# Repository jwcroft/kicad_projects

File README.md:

# kicad_projects
Incremental backups in case kicad decides to break itself again...

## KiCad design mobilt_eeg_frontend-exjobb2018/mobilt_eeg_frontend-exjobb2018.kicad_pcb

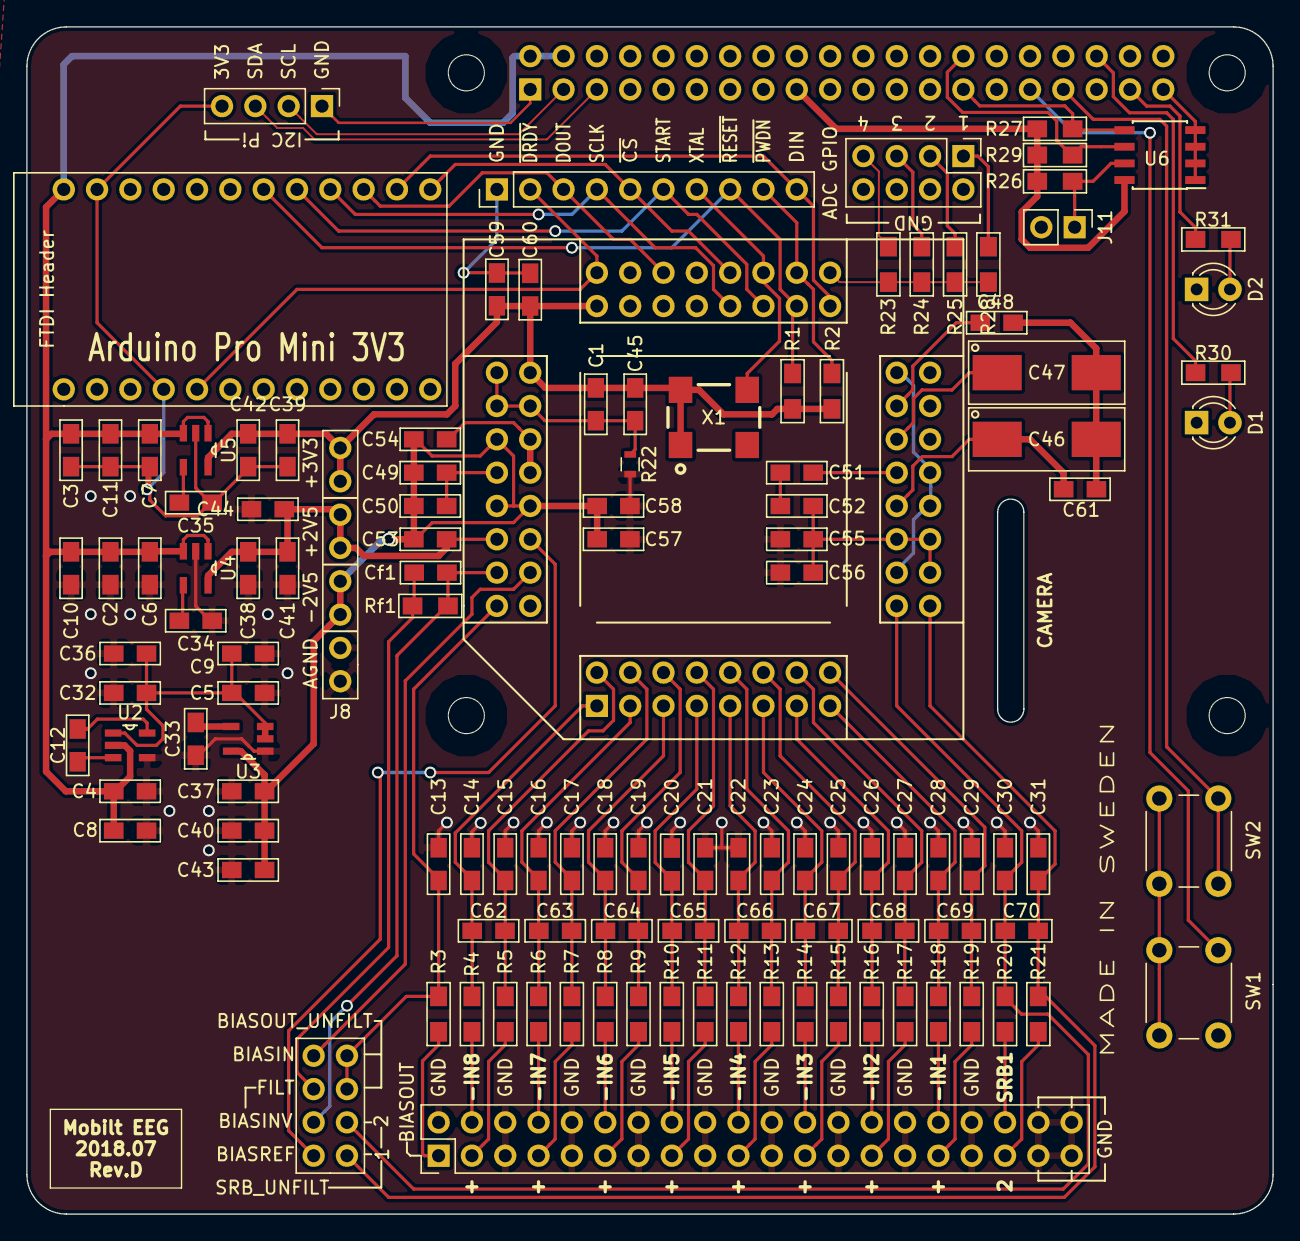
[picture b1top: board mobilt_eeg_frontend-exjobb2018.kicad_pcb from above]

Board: 2 copper layers, 95.0 x 90.5 mm, 127 parts (1 on the bottom side), 84 nets.

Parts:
C1, C10, C11, C43, C44, C50, C56, C58, C60, C61: 100nF; C_0805_HandSoldering_enclosed_footprint
C2, C3, C4, C5, C32, C37, C38, C39: 10uF; C_0805_HandSoldering_enclosed_footprint
C6, C7, C8, C12, C36, C45, C48, C49, C51, C52, C53, C54, C55, C57, C59: 1uF; C_0805_HandSoldering_enclosed_footprint
C9, C40, C41, C42: 2.2uF; C_0805_HandSoldering_enclosed_footprint
C13, C14, C15, C16, C17, C18, C19, C20, C21, C22, C23, C24, C25, C26, C27, C28, C29, C30, C31: 4.7nF; C_0805_HandSoldering_enclosed_footprint
C33, C34, C35: 10nF; C_0805_HandSoldering_enclosed_footprint
C46: 10uF; CP_Tantalum_Case-D_EIA-7343-31_Hand
C47: 100uF; CP_Tantalum_Case-D_EIA-7343-31_Hand
C62, C63, C64, C65, C66, C67, C68, C69, C70: DNP; C_0805_HandSoldering_enclosed_footprint
Cf1: 1.5nF; C_0805_HandSoldering_enclosed_footprint
D1, D2: LED; LED_D3.0mm
J1, J3: Conn_02x04_Odd_Even; Pin_Header_Straight_2x04_Pitch2.54mm
J2: Conn_02x20_Odd_Even; Pin_Header_Straight_2x20_Pitch2.54mm
J5: Data Header; Pin_Header_Straight_1x10_Pitch2.54mm
J8: Conn_01x08; Pin_Header_Straight_1x08_Pitch2.54mm
J9: Conn_01x04; Pin_Header_Straight_1x04_Pitch2.54mm
J11: Conn_01x02; Pin_Header_Straight_1x02_Pitch2.54mm
MK1, MK2, MK3, MK4: M2.5; MountingHole_2.7mm_M2.5
P1: Conn_02x20_Odd_Even; PinSocket_2x20_P2.54mm_Vertical
R1, R2, R23, R24, R25, R26, R28: 10k; R_0805_HandSoldering_enclose_footprint
R3, R4, R5, R6, R7, R8, R9, R10, R11, R12, R13, R14, R15, R16, R17, R18, R19, R20, R21: 4.99k 1%; R_0805_HandSoldering_enclose_footprint
R22: 0; R_0603
R27, R29: 3.9k; R_0805_HandSoldering_enclose_footprint
R30, R31: 1k; R_0805_HandSoldering_enclose_footprint
Rf1: 1M; R_0805_HandSoldering_enclose_footprint
SW1, SW2: SW_DIP_x01; SW_PUSH_6mm_h5mm
U1: ADS1299-4PAG; xQFP_64_to_2.54mm_adapter
U2: TPS60403DBVR; SOT95P280X145-5N
U3: TPS72325DBVT; SOT95P280X145-5N
U4: TPS73225DBVT; SOT95P280X145-5N
U5: TPS73233DBVT; SOT95P280X145-5N
U6: CAT24C256; SOIC-8_3.9x4.9mm_Pitch1.27mm
U7: arduino_pro_mini_3V3_sparkfun
X1: X1G0044810050_SG7050CAN_2.048_MHZ; SG0705

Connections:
+5V: C2.1, C3.1, C4.1, C6.1, C7.1, C8.1, C10.1, C11.1, P1.2, P1.4, U2.2, U4.1, U4.3, U5.1, U5.3, U7.24
/+3V3_Pi: J9.1, P1.1, P1.17, R26.2, R27.1, R29.1, U6.8
/-5V_unreg: C5.1, C9.1, C32.1, C36.1, U2.1, U3.2, U3.3
/BIASIN: J3.8, U1.62
/BIASINV: Cf1.1, J3.4, Rf1.1, U1.61
/BIASOUT: C13.1, J3.5, J3.7, R3.1, U1.63
/BIASOUT_FILTERED: J2.1, R3.2
/BIASREF: J3.2, U1.60
/GPIO1: J1.1, R28.2, U1.42
/GPIO2: J1.3, R25.2, U1.44
/GPIO2(SDA1): J9.2, P1.3
/GPIO3: J1.5, R24.2, U1.45
/GPIO3(SCL1): J9.3, P1.5
/GPIO4: J1.7, R23.2, U1.46
/GPIO6: P1.31, SW1.1
/GPIO13(PWM1): P1.33, SW2.1
/GPIO16: P1.36, R30.2
/GPIO26: P1.37, R31.2
/ID_SC: P1.28, R29.2, U6.6
/ID_SD: P1.27, R27.2, U6.5
/IN1N: C28.1, C69.1, R18.1, U1.15
/IN1P: C29.2, C69.2, R19.1, U1.16
/IN2N: C26.1, C68.1, R16.1, U1.13
/IN2P: C27.2, C68.2, R17.1, U1.14
/IN3N: C24.1, C67.1, R14.1, U1.11
/IN3P: C25.2, C67.2, R15.1, U1.12
/IN4N: C22.1, C66.1, R12.1, U1.9
/IN4P: C23.2, C66.2, R13.1, U1.10
/IN5N: C20.1, C65.1, R10.1, U1.7
/IN5P: C21.2, C65.2, R11.1, U1.8
/IN6N: C18.1, C64.1, R8.1, U1.5
/IN6P: C19.2, C64.2, R9.1, U1.6
/IN7N: C16.1, C63.1, R6.1, U1.3
/IN7P: C17.2, C63.2, R7.1, U1.4
/IN8N: C14.1, C62.1, R4.1, U1.1
/IN8P: C15.2, C62.2, R5.1, U1.2
/SPI_MISO: J5.3, U7.15
/SPI_MOSI: J5.10, U7.14
/SPI_SCK: J5.4, U1.40, U7.16
/SPI_SS: J5.5, U1.39, U7.13
/SRB1: C31.2, C70.2, J3.1, R21.1, U1.17
/SRB1_FILT: J2.36, R20.2
/SRB2: C30.1, C70.1, J3.3, R20.1, U1.18
/SRB2_FILT: J2.35, R21.2
/START: J5.6, P1.26, U1.38, U7.17
/VCAP1: C47.1, U1.28
/VCAP2: C48.2, U1.30
/VCAP3: C49.2, C50.2, U1.55
/VCAP4: C51.2, U1.26
/VREFP: C46.1, C61.1, U1.24
/XTAL: J5.7, U1.37, X1.3
/~DRDY: J5.2, U1.47, U7.5
/~PWDN: J5.9, P1.32, R2.2, U1.35, U7.19
/~RESET: J5.8, P1.29, R1.2, U1.36, U7.18
AGND: C2.2, C4.2, C5.2, C6.2, C8.2, C9.2, C10.2, C13.2, C14.2, C15.1, C16.2, C17.1, C18.2, C19.1, C20.2, C21.1, C22.2, C23.1, C24.2, C25.1, C26.2, C27.1, C28.2, C29.1, C30.2, C31.1, C32.2, C33.2, C34.2, C36.2, C37.2, C38.2, C40.2, C41.2, C43.2, C44.2, C55.1, C56.1, C57.1, C58.1, J2.2, J2.5, J2.6, J2.9, J2.10, J2.13, J2.14, J2.17, J2.18, J2.21, J2.22, J2.25, J2.26, J2.29, J2.30, J2.33, J2.34, J2.37, J2.38, J2.39, J2.40, J8.1, J8.2, R22.2, U2.4, U3.1, U4.2
AVDD: C38.1, C41.1, C44.1, C52.2, C53.2, C54.2, C55.2, C56.2, J8.5, J8.6, U1.19, U1.21, U1.22, U1.54, U1.56, U1.59, U4.5
AVSS: C37.1, C40.1, C43.1, C46.2, C47.2, C48.1, C49.1, C50.1, C51.1, C52.1, C53.1, C54.1, C57.2, C58.2, C61.2, J8.3, J8.4, U1.20, U1.23, U1.25, U1.32, U1.53, U1.57, U1.58, U3.5
DGND: C1.2, C3.2, C7.2, C11.2, C35.2, C39.2, C42.2, C45.2, C59.1, C60.1, D1.1, D2.1, J1.2, J1.4, J1.6, J1.8, J5.1, J9.4, J11.2, P1.6, P1.9, P1.14, P1.20, P1.25, P1.30, P1.34, P1.39, R22.1, R23.1, R24.1, R25.1, R28.1, SW1.2, SW2.2, U1.31, U1.33, U1.41, U1.49, U1.51, U1.52, U5.2, U6.1, U6.2, U6.3, U6.4, U7.4, U7.23, X1.2
DVDD: C1.1, C39.1, C42.1, C45.1, C59.2, C60.2, J8.7, J8.8, R1.1, R2.1, U1.48, U1.50, U5.5, X1.1, X1.4
unnamed: C12.1, U2.3
unnamed: C12.2, U2.5
unnamed: C33.1, U3.4
unnamed: C34.1, U4.4
unnamed: C35.1, U5.4
unnamed: Cf1.2, J3.6, Rf1.2
unnamed: D1.2, R30.1
unnamed: D2.2, R31.1
unnamed: J2.3, R5.2
unnamed: J2.4, R4.2
unnamed: J2.7, R7.2
unnamed: J2.8, R6.2
unnamed: J2.11, R9.2
unnamed: J2.12, R8.2
unnamed: J2.15, R11.2
unnamed: J2.16, R10.2
unnamed: J2.19, R13.2
unnamed: J2.20, R12.2
unnamed: J2.23, R15.2
unnamed: J2.24, R14.2
unnamed: J2.27, R17.2
unnamed: J2.28, R16.2
unnamed: J2.31, R19.2
unnamed: J2.32, R18.2
unnamed: J11.1, R26.1, U6.7

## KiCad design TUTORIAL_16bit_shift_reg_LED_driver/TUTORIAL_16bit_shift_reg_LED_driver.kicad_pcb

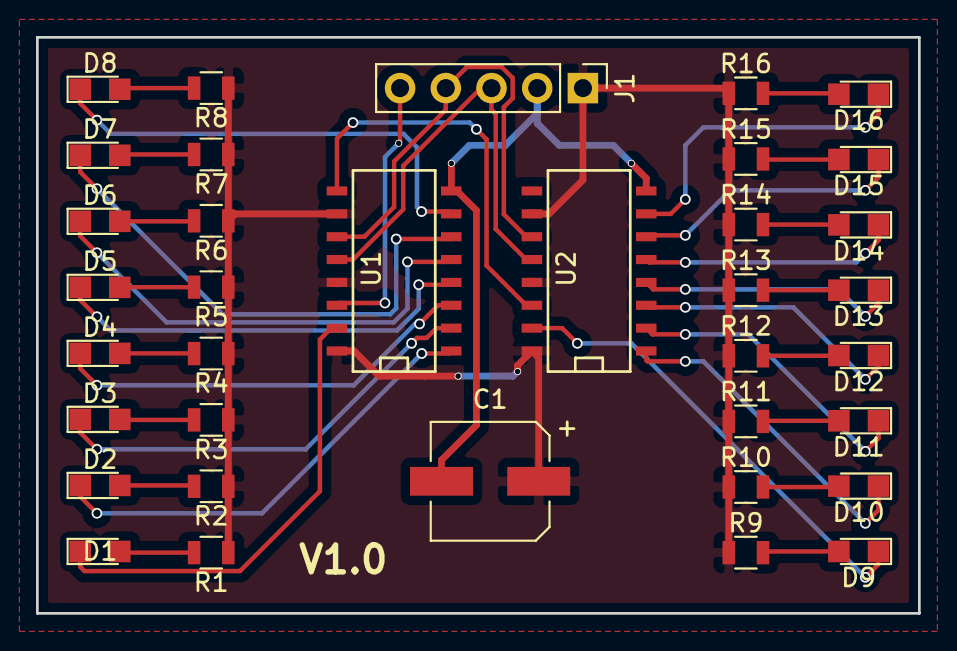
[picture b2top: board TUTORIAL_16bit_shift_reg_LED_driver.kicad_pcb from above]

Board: 2 copper layers, 49.0 x 32.0 mm, 36 parts (0 on the bottom side), 38 nets.

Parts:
C1: 200uF; CP_Elec_6.3x5.3
D1, D2, D3, D4, D5, D6, D7, D8, D9, D10, D11, D12, D13, D14, D15, D16: LED_ALT; LED_0805
J1: Conn_01x05_Male; Pin_Header_Straight_1x05_Pitch2.54mm
R1, R2, R3, R4, R5, R6, R7, R8, R9, R10, R11, R12, R13, R14, R15, R16: R; R_0805
U1, U2: 74HC595; SO-16-N

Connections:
/CLOCK: J1.4, U1.11, U2.11
/DATA: J1.5, U1.14
/DATA_S: U1.9, U2.14
/LATCH: J1.3, U1.12, U2.12
/led_1_1: D1.1, U1.15
/led_1_2: D2.1, U1.1
/led_1_3: D3.1, U1.2
/led_1_4: D4.1, U1.3
/led_1_5: D5.1, U1.4
/led_1_6: D6.1, U1.5
/led_1_7: D7.1, U1.6
/led_1_8: D8.1, U1.7
/led_2_1: D9.1, U2.15
/led_2_2: D10.1, U2.1
/led_2_3: D11.1, U2.2
/led_2_4: D12.1, U2.3
/led_2_5: D13.1, U2.4
/led_2_6: D14.1, U2.5
/led_2_7: D15.1, U2.6
/led_2_8: D16.1, U2.7
GND: C1.2, J1.2, U1.8, U2.8
unnamed: D1.2, R1.2
unnamed: D2.2, R2.2
unnamed: D3.2, R3.2
unnamed: D4.2, R4.2
unnamed: D5.2, R5.2
unnamed: D6.2, R6.2
unnamed: D7.2, R7.2
unnamed: D8.2, R8.2
unnamed: D9.2, R9.2
unnamed: D10.2, R10.2
unnamed: D11.2, R11.2
unnamed: D12.2, R12.2
unnamed: D13.2, R13.2
unnamed: D14.2, R14.2
unnamed: D15.2, R15.2
unnamed: D16.2, R16.2
VCC: C1.1, J1.1, R1.1, R2.1, R3.1, R4.1, R5.1, R6.1, R7.1, R8.1, R9.1, R10.1, R11.1, R12.1, R13.1, R14.1, R15.1, R16.1, U1.10, U1.13, U1.16, U2.10, U2.13, U2.16

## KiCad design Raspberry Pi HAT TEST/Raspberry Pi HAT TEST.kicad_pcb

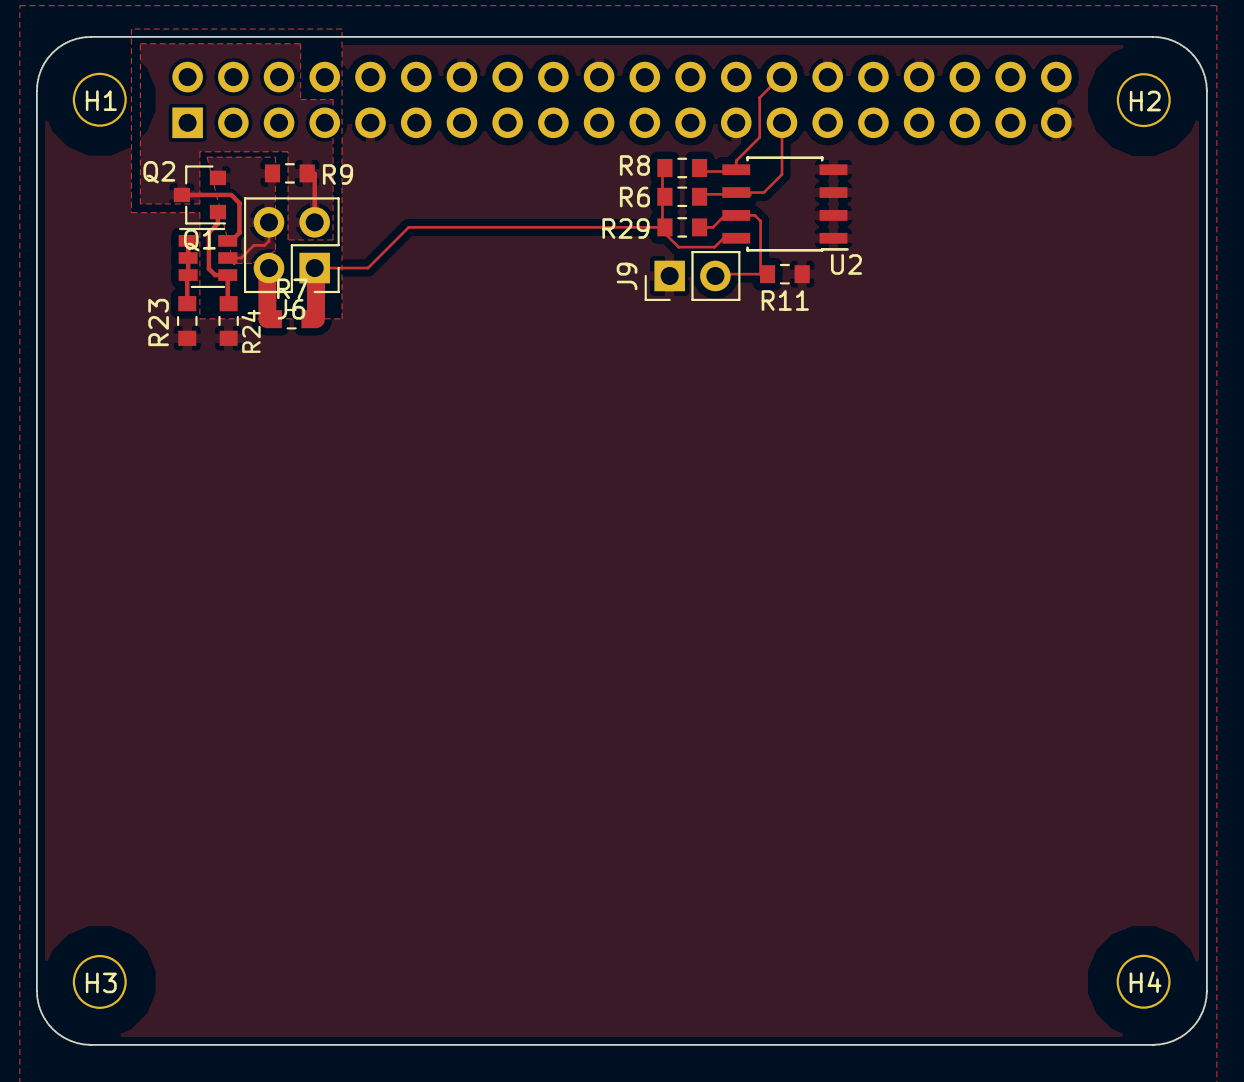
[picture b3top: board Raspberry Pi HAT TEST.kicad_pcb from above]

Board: 4 copper layers, 65.0 x 56.0 mm, 18 parts (1 on the bottom side), 10 nets.

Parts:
H1, H2, H3, H4: 3mm_Mounting_Hole; NPTH_3mm_ID
J3: 40HAT; PinSocket_2x20_P2.54mm_Vertical
J6: CONN_02X02; PinHeader_2x02_P2.54mm_Vertical
J9: CONN_01X02; PinHeader_1x02_P2.54mm_Vertical
Q1: DMG2305UX; SOT-23
Q2: DMMT5401; SOT-23-6
R6, R8: 3.9K; R_0603_1608Metric_Pad0.84x1.00mm_HandSolder
R7, R9, R11: DNP; R_0603_1608Metric_Pad0.84x1.00mm_HandSolder
R23, R24: 22; R_0603_1608Metric_Pad0.84x1.00mm_HandSolder
R29: 10K; R_0603_1608Metric_Pad0.84x1.00mm_HandSolder
U2: CAT24C32; SOIC-8_3.9x4.9mm_P1.27mm

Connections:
/ID_SC_EEPROM: J3.28, R8.2, U2.5
/ID_SD_EEPROM: J3.27, R6.2, U2.6
/P3V3: J6.1, R6.1, R7.2, R8.1, R29.1, U2.8
/P3V3_HAT: J3.1, J6.2, R7.1
/P5V: J6.3, Q1.3, Q2.6, R9.2
/P5V_HAT: J3.2, J3.4, J6.4, Q1.2, Q2.5, R9.1
GND: J3.6, J3.9, J3.14, J3.20, J3.25, J3.30, J3.34, J3.39, J9.1, R11.2, R23.2, R24.2, U2.1, U2.2, U2.3, U2.4
unnamed: J9.2, R11.1, R29.2, U2.7
unnamed: Q1.1, Q2.4, R24.1
unnamed: Q2.1, Q2.2, Q2.3, R23.1

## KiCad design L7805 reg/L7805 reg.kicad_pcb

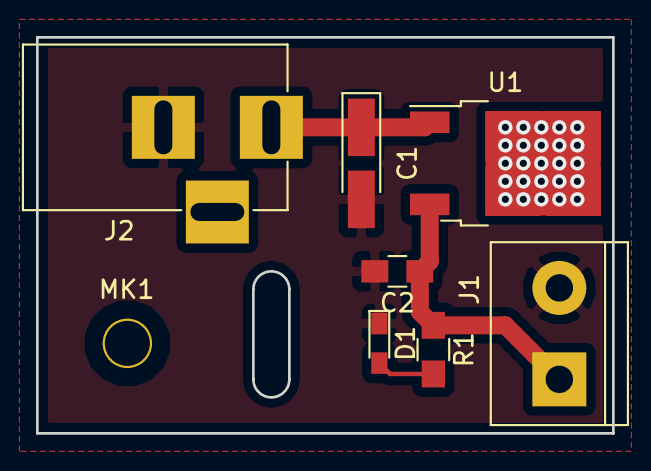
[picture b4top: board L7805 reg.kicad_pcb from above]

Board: 2 copper layers, 32.0 x 22.0 mm, 8 parts (0 on the bottom side), 4 nets.

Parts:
C1: 0,33uF; CP_Tantalum_Case-A_EIA-3216-18_Hand
C2: 0,1uF; C_0805_HandSoldering
D1: LED; LED_0603_HandSoldering
J1: Screw_Terminal_01x02; TerminalBlock_bornier-2_P5.08mm
J2: Barrel_Jack; BARREL_JACK
MK1: Mounting_Hole; Mounting_Hole_Keepout
R1: 270; R_0805_HandSoldering
U1: L7805; TO-252-2

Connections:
+12V: C1.1, J2.1, U1.1
GND: C1.2, C2.2, D1.1, J1.2, J2.2, U1.2
unnamed: C2.1, J1.1, R1.1, U1.3
unnamed: D1.2, R1.2

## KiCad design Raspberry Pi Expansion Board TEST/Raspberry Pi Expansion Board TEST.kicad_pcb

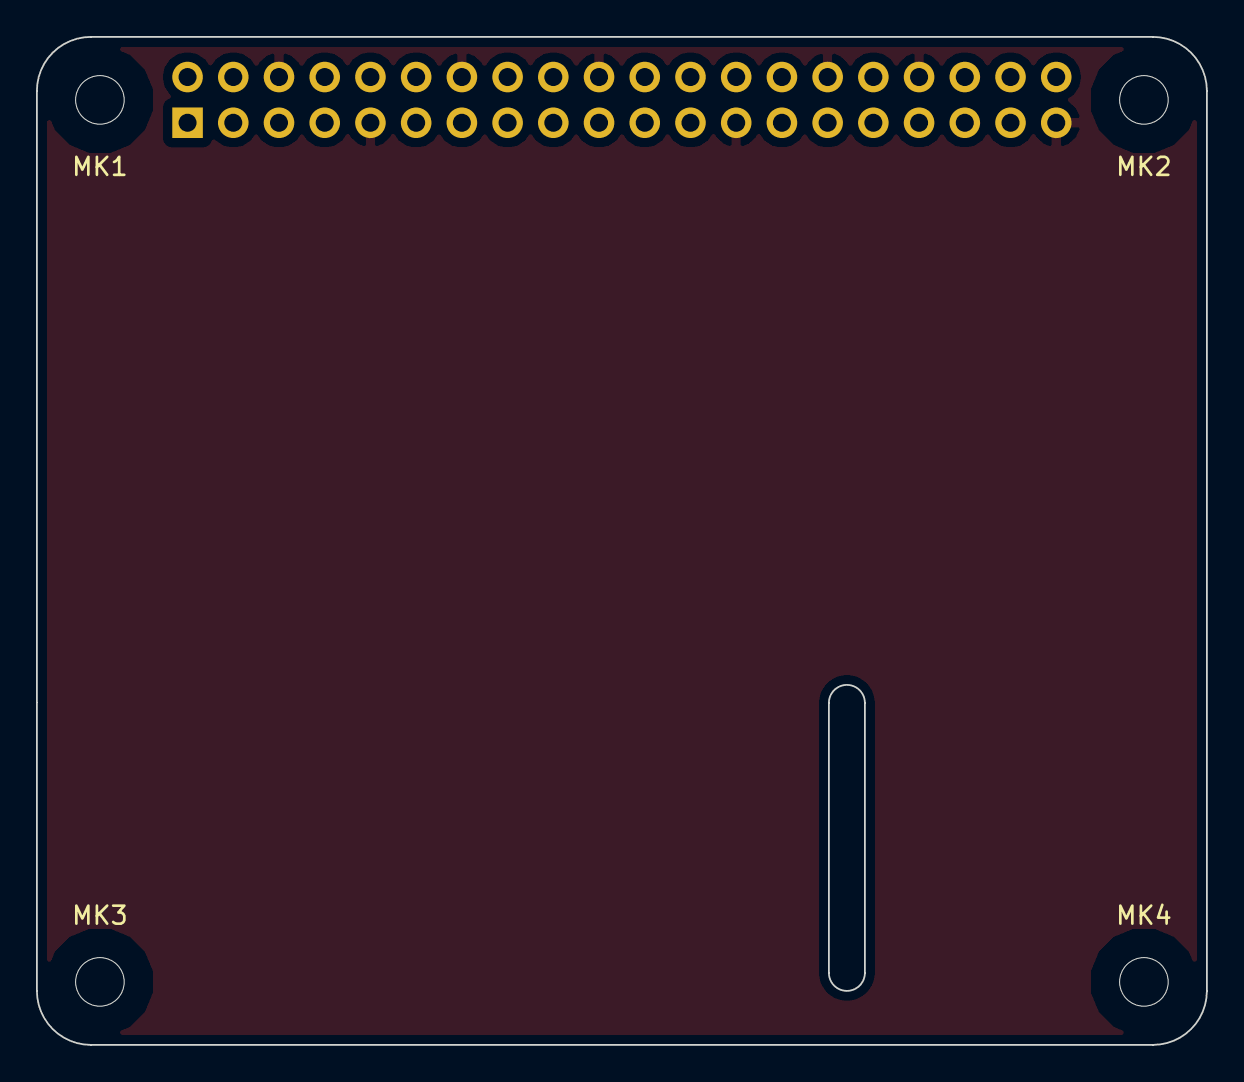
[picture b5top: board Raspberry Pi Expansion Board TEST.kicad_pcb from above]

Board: 2 copper layers, 65.0 x 56.0 mm, 5 parts (1 on the bottom side), 3 nets, no tracks yet.

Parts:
MK1, MK2, MK3, MK4: M2.5; MountingHole_2.7mm_M2.5
P1: Conn_02x20_Odd_Even; PinSocket_2x20_P2.54mm_Vertical

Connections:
+3V3: P1.1, P1.17
+5V: P1.2, P1.4
GND: P1.6, P1.9, P1.14, P1.20, P1.25, P1.30, P1.34, P1.39

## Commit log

2018-07-08 Push all local files
2018-07-08 Time to assign fottprints to schematic symbols.
2018-07-08 tryin to create my own footprints...
2018-07-08 backup
2018-07-08 new backup
2018-07-09 experimented with creating a board from start to finish (L7805 proj.)
2018-07-09 Boring kicad setup for raspi expansion board: *removed screen cutout. *comfirmed all important board dimensions. *enlarged mounting hole clearance area to match spec. *set design rules according to p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
2018-07-10 Tested associating 3d model with footprint CAT24C32 in HAT TEST.
2018-07-10 a bunch of experimentation
2018-07-10 Updated dir_tree script.
2018-07-10 removed UL stuff.
2018-07-10 created custom SG0705CAN symbol for EESCHEMA
2018-07-10 completed oscillator symbol with all doc. fields.
2018-07-10 Crash averted!
2018-07-10 plz no crash now.
2018-07-11 Goodnight.
2018-07-11 did another bloody tutorial...
2018-07-11 added electrode intermediate pin-headers
2018-07-11 gettin paranoid about .... crashes!
2018-07-11 created analog/digital power symbols (copy&pasted between files)
2018-07-11 that's enough for now. Next: read datasheets thoroughly
2018-07-12 done some stuff... it would be a shame if anything happened to it....
2018-07-12 Before annotation.
2018-07-12 beginning to understand the big picture... life, the universe, everything...
2018-07-13 back it up my dude
2018-07-13 before new annotation
2018-07-13 assigned PCB footprints
2018-07-13 before importing netlist to PCBNEW
2018-07-13 1/3 way there...
2018-07-13 took out CLKSEL jumper
2018-07-13 Enough for today.
2018-07-16 backup the weeknd
2018-07-16 almost doonnnneeee!!!
2018-07-17 labeled some headers/moved some silk covering pads
2018-07-17 fine tuning etc...
2018-07-17 moved some silk
2018-07-18 added differential capacitors on each channel with DNP value.
2018-07-18 push
2018-07-19 Changed footprints for resistors and caps to one that encloses the pads.
2018-07-19 rsync backup script
2018-07-19 trivial change to test branch
2018-07-19 push for sk00l
2018-07-19 done sum stuff
2018-07-19 locked mounting holes and pi header.
2018-07-21 eagle import experiments
2018-07-21 label MASTER pcb layout as opposed to ALT-PCB
2018-07-25 adjusted bias header to conform to 2.54 grid
2018-07-25 before nightly update
2018-07-26 MADE IN SWEDEN
2018-07-31 Gave caps and resistors custom footprint assignment. created arduino pro mini 3v3 sparkfun module in schema and pcb footprint. Deleted extraneous vias.
2018-07-31 starting to shift things around in preparation for grid alignment
2018-07-31 Aligned a few things to new grid system. Tested arduino footprint suitability.
2018-07-31 savea
2018-07-31 fixed pour
2018-08-01 savea baa
2018-08-01 savea for faen
2018-08-07 Aligned most stuff except power supply.
2018-08-07 Added a few more traces and GND vias.
2018-08-07 Added a few traces, replaced a remaining GNDD to DGND.
2018-08-07 savea nu baa
2018-08-07 Aligned PSU sections in individual "columns" and aligned to 1mm grid .
2018-08-07 stuffelistuff
2018-08-08 what even is this?
2018-08-08 BLEH
2018-08-13 Connect 3V3 reg to arduino
2018-08-13 Moving all comms to microcontroller
2018-08-13 OVERHAUL! mang
2018-08-29 savea lite bara bara
2019-02-13 connected hanging AVDD
2019-02-13 loose connections
2019-02-28 extended copper pour
2019-03-07 asdlögasfj
2019-04-28 dunno what's changed
2019-04-28 Managed to make changes despite myself
